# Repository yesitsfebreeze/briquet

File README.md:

# Briquet
This is a small footprint wireless 30% keyboard.  
The default layout aims to be very consistent to a querty layout.  

# Configuration
You can clone this repository and authorize it on:  
https://nickcoutsos.github.io/keymap-editor/  
Once u save the firmware and keymap render will automatically be built for you.  

# Renders

# Default keymap

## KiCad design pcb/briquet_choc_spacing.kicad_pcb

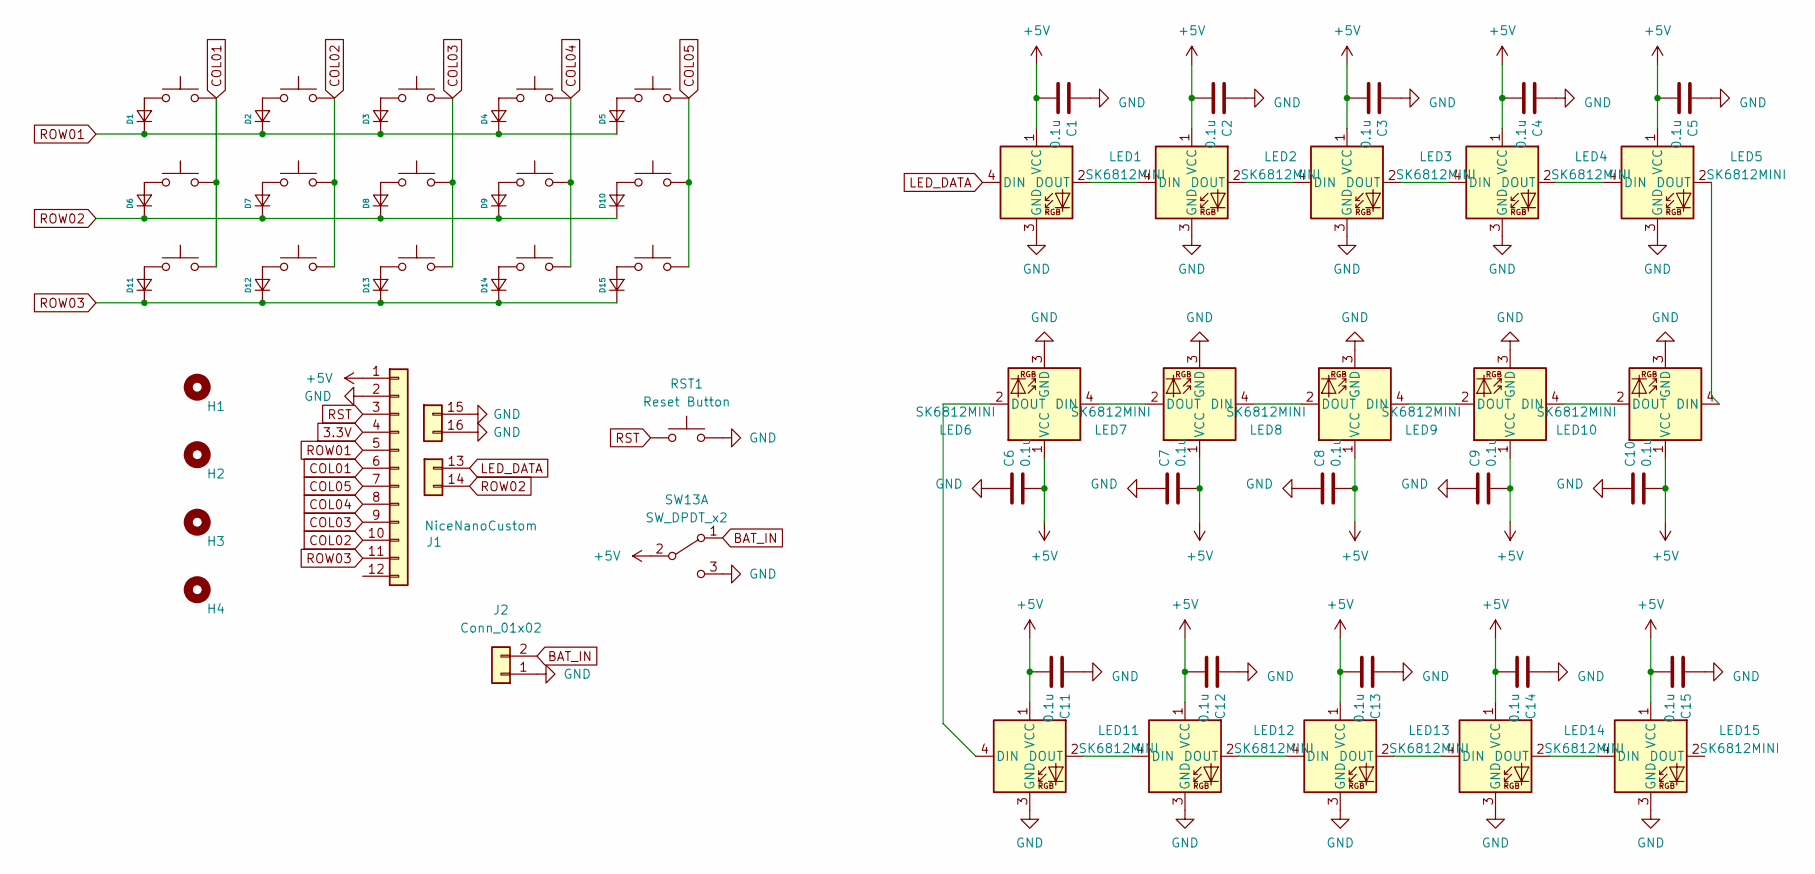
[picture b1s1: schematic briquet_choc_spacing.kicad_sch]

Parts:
C1, C2, C3, C4, C5, C6, C7, C8, C9, C10, C11, C12, C13, C14, C15: 0.1u; C_0402_1005Metric
CHOC1, CHOC2, CHOC3, CHOC4, CHOC5, CHOC6, CHOC7, CHOC8, CHOC9, CHOC10, CHOC11, CHOC12, CHOC13, CHOC14, CHOC15: CHOC; ChocHotSwap
D1, D2, D3, D4, D5, D6, D7, D8, D9, D10, D11, D12, D13, D14, D15: D_Small; D_SOD-123; Digi-Key_PN 1N4148WTPMSCT-ND
H1, H2, H3, H4: MountingHole; Mount
J1: NiceNanoCustom
J2: Conn_01x02; BatConnection
LED1, LED2, LED3, LED4, LED5, LED6, LED7, LED8, LED9, LED10, LED11, LED12, LED13, LED14, LED15: SK6812MINI; Led
RST1: Reset Button; SW_Push_SPST_NO_Alps_SKRK
SW13: SW_DPDT_x2; PCM12_dip_switch

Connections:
3.3V: J1.4
+5V: C1.2, C2.2, C3.2, C4.2, C5.2, C6.2, C7.2, C8.2, C9.2, C10.2, C11.2, C12.2, C13.2, C14.2, C15.2, J1.1, LED1.1 (VCC), LED2.1 (VCC), LED3.1 (VCC), LED4.1 (VCC), LED5.1 (VCC), LED6.1 (VCC), LED7.1 (VCC), LED8.1 (VCC), LED9.1 (VCC), LED10.1 (VCC), LED11.1 (VCC), LED12.1 (VCC), LED13.1 (VCC), LED14.1 (VCC), LED15.1 (VCC), SW13.2 (B)
BAT_IN: J2.2, SW13.1 (A)
COL01: CHOC1.2, CHOC6.2, CHOC11.2, J1.6
COL02: CHOC2.2, CHOC7.2, CHOC12.2, J1.10
COL03: CHOC3.2, CHOC8.2, CHOC13.2, J1.9
COL04: CHOC4.2, CHOC9.2, CHOC14.2, J1.8
COL05: CHOC5.2, CHOC10.2, CHOC15.2, J1.7
GND: C1.1, C2.1, C3.1, C4.1, C5.1, C6.1, C7.1, C8.1, C9.1, C10.1, C11.1, C12.1, C13.1, C14.1, C15.1, J1.2, J1.15, J1.16, J2.1, LED1.3 (GND), LED2.3 (GND), LED3.3 (GND), LED4.3 (GND), LED5.3 (GND), LED6.3 (GND), LED7.3 (GND), LED8.3 (GND), LED9.3 (GND), LED10.3 (GND), LED11.3 (GND), LED12.3 (GND), LED13.3 (GND), LED14.3 (GND), LED15.3 (GND), RST1.2, SW13.3 (C)
LED_DATA: J1.13, LED1.4 (DIN)
unnamed: CHOC1.1, D1.2 (A)
unnamed: CHOC2.1, D2.2 (A)
unnamed: CHOC3.1, D3.2 (A)
unnamed: CHOC4.1, D4.2 (A)
unnamed: CHOC5.1, D5.2 (A)
unnamed: CHOC6.1, D6.2 (A)
unnamed: CHOC7.1, D7.2 (A)
unnamed: CHOC8.1, D8.2 (A)
unnamed: CHOC9.1, D9.2 (A)
unnamed: CHOC10.1, D10.2 (A)
unnamed: CHOC11.1, D11.2 (A)
unnamed 21: CHOC12.1, D12.2 (A); also elsewhere on the board
unnamed 22: CHOC13.1, D13.2 (A); also elsewhere on the board
unnamed: CHOC14.1, D14.2 (A)
unnamed: CHOC15.1, D15.2 (A)
unnamed: LED1.2 (DOUT), LED2.4 (DIN)
unnamed: LED2.2 (DOUT), LED3.4 (DIN)
unnamed: LED3.2 (DOUT), LED4.4 (DIN)
unnamed: LED4.2 (DOUT), LED5.4 (DIN)
unnamed: LED6.4 (DIN), LED7.2 (DOUT)
unnamed: LED7.4 (DIN), LED8.2 (DOUT)
unnamed: LED8.4 (DIN), LED9.2 (DOUT)
unnamed: LED5.2 (DOUT), LED10.4 (DIN)
unnamed: LED9.4 (DIN), LED10.2 (DOUT)
unnamed: LED6.2 (DOUT), LED11.4 (DIN)
unnamed: LED11.2 (DOUT), LED12.4 (DIN)
unnamed: LED12.2 (DOUT), LED13.4 (DIN)
unnamed: LED13.2 (DOUT), LED14.4 (DIN)
unnamed: LED14.2 (DOUT), LED15.4 (DIN)
ROW01: D1.1 (K), D2.1 (K), D3.1 (K), D4.1 (K), D5.1 (K), J1.5
ROW02: D6.1 (K), D7.1 (K), D8.1 (K), D9.1 (K), D10.1 (K), J1.14
ROW03: D11.1 (K), D12.1 (K), D13.1 (K), D14.1 (K), D15.1 (K), J1.11; also elsewhere on the board
RST: J1.3, RST1.1

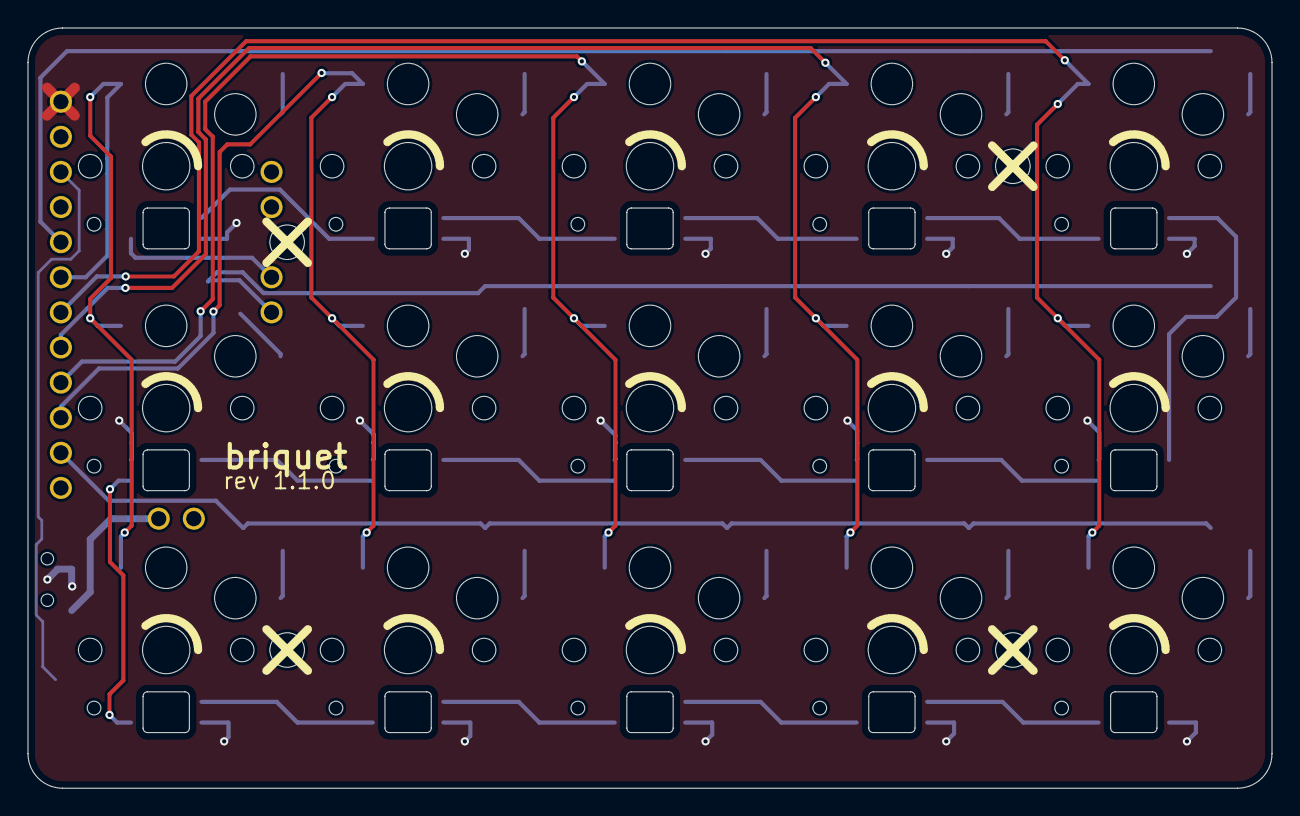
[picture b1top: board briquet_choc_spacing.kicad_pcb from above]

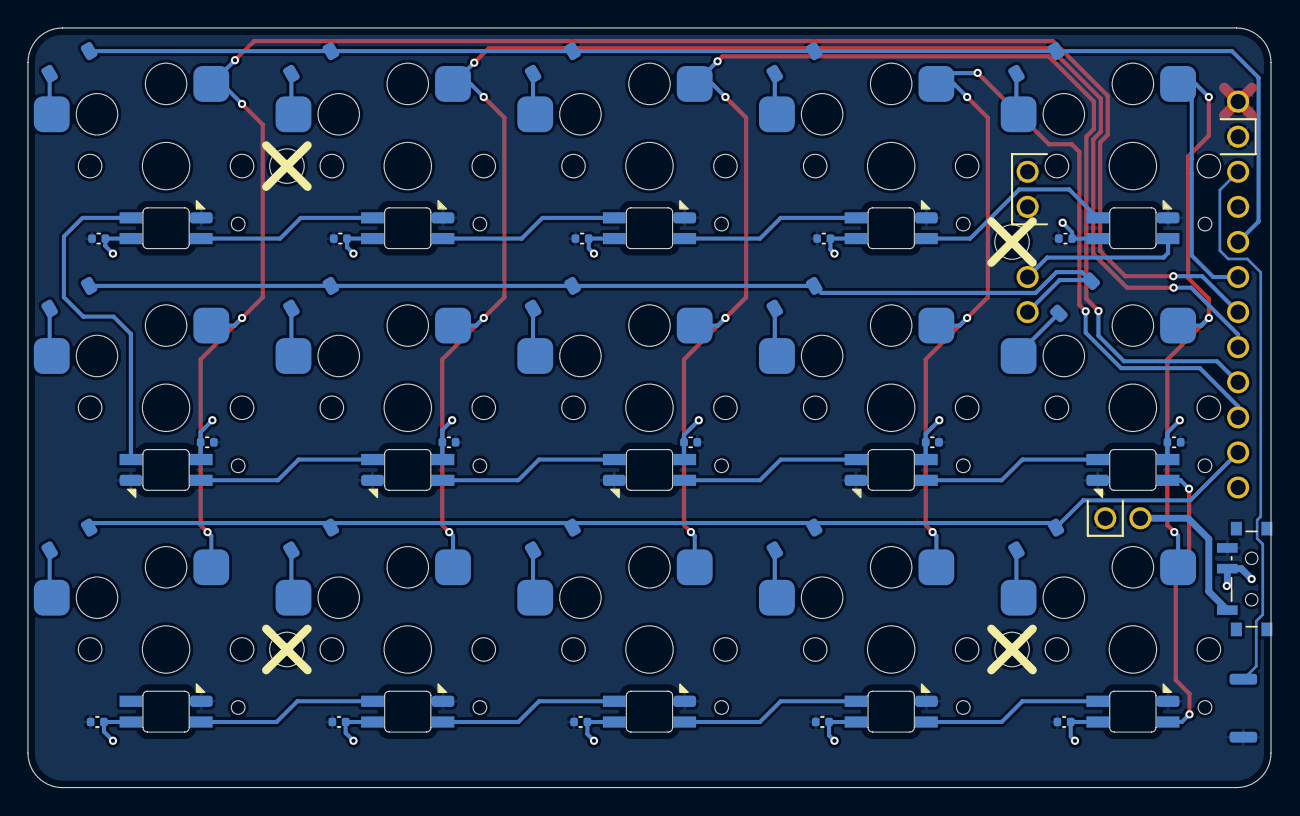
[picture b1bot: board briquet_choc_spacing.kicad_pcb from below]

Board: 2 copper layers, 90.0 x 55.0 mm, 68 parts (63 on the bottom side), 42 nets.

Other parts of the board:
D114,5, D114,5#2: D_Small; D_SOD-123

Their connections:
unnamed 21: D114,5.2 (A); also elsewhere on the board
unnamed 22: D114,5#2.2 (A); also elsewhere on the board
ROW03: D114,5.1 (K), D114,5#2.1 (K); also elsewhere on the board

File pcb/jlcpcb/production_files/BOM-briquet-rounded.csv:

Comment,Designator,Footprint,LCSC
0.1u,"C1,C10,C11,C12,C13,C14,C15,C2,C3,C4,C5,C6,C7,C8,C9",C_0402_1005Metric,C14445
Reset Button,RST1,SW_Push_SPST_NO_Alps_SKRK,C231329
SK6812MINI,"LED1,LED10,LED11,LED12,LED13,LED14,LED15,LED2,LED3,LED4,LED5,LED6,LED7,LED8,LED9",Led,C5149201
CHOC,"CHOC1,CHOC10,CHOC11,CHOC12,CHOC13,CHOC14,CHOC15,CHOC2,CHOC3,CHOC4,CHOC5,CHOC6,CHOC7,CHOC8,CHOC9",ChocHotSwap,C5333465
D_Small,"D1,D10,D11,D12,D13,D14,D15,D2,D3,D4,D5,D6,D7,D8,D9",D_SOD-123,C83528
SW_DPDT_x2,SW13,PCM12_dip_switch,C963206

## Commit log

2023-11-25 Initial User Config.
2023-12-02 adding files
2023-12-02 keymap-drawer render
2023-12-02 Updated briquet.keymap
2023-12-08 pinout
